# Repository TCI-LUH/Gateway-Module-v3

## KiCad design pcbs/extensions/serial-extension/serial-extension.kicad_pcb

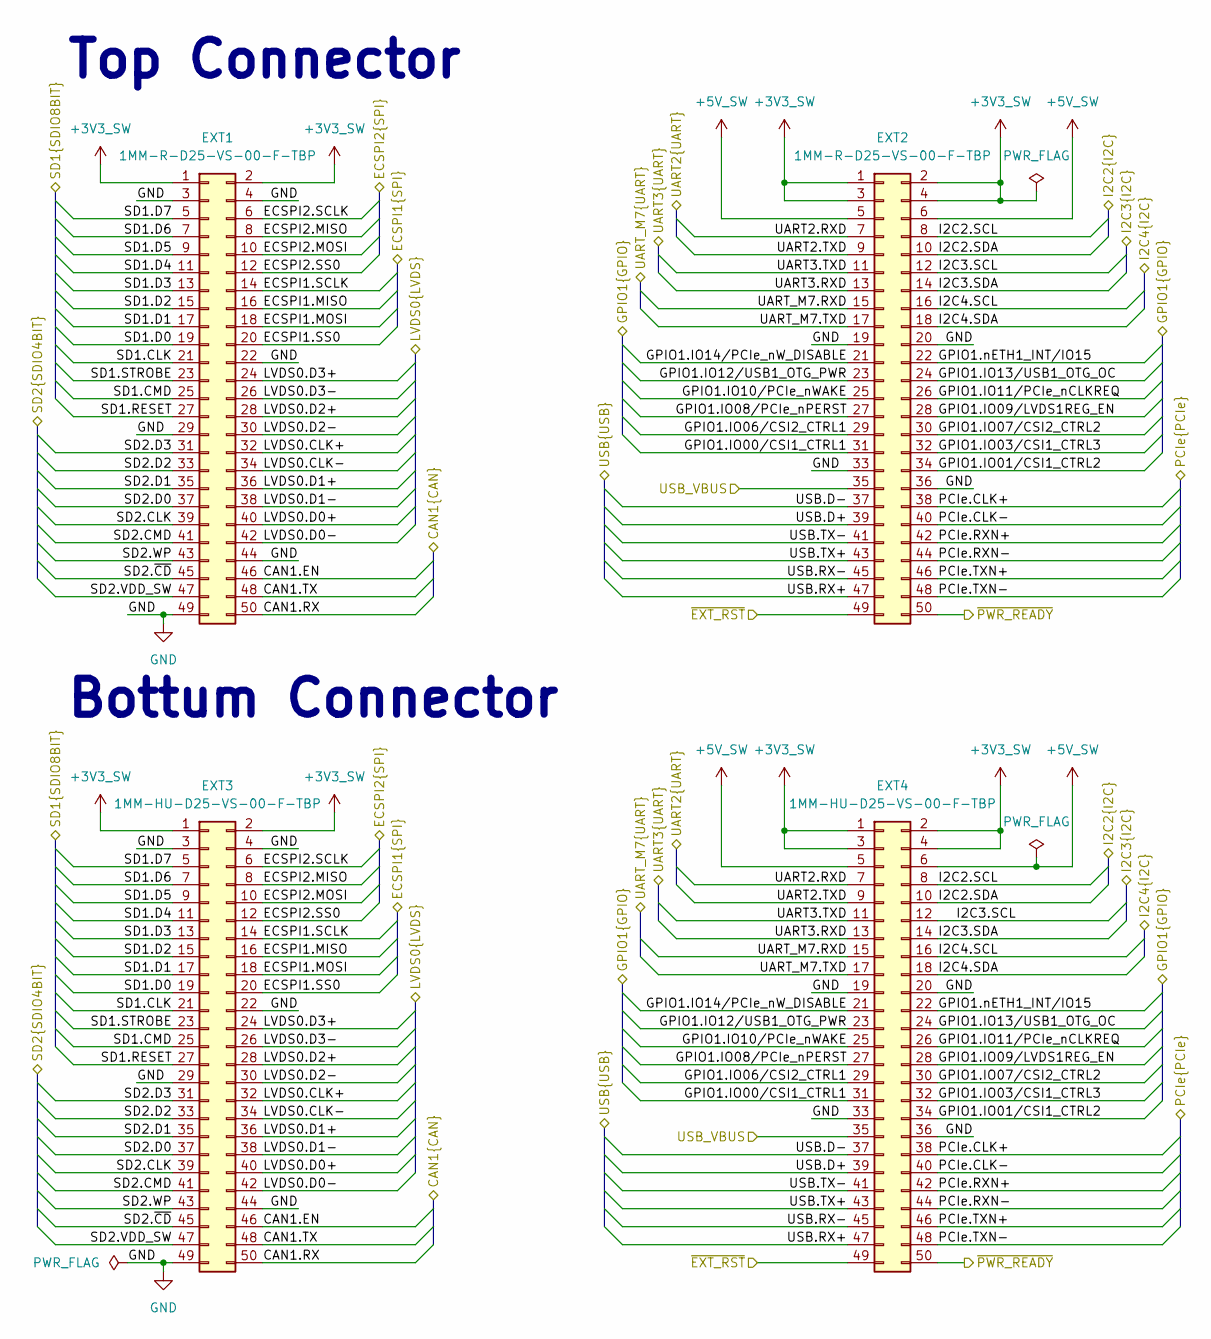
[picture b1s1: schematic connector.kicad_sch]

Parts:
EXT1, EXT2: 1MM-R-D25-VS-00-F-TBP; 1MMRD25VS00FTBP; Mouser Part Number 571-1MMRD25VS00FTBP
EXT3, EXT4: 1MM-HU-D25-VS-00-F-TBP; 1MMHUD25VS00FTBP; Mouser Part Number 571-1MMRD25VS00FTBP

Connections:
+3V3_SW: EXT1.1, EXT1.2, EXT2.1, EXT2.2, EXT2.3, EXT2.4, EXT3.1, EXT3.2, EXT4.1, EXT4.2, EXT4.3, EXT4.4; also elsewhere on the board
+5V_SW: EXT2.5, EXT2.6, EXT4.5, EXT4.6
/connector/CAN1.EN: EXT1.46, EXT3.46
/connector/CAN1.RX: EXT1.50, EXT3.50
/connector/CAN1.TX: EXT1.48, EXT3.48
/connector/ECSPI1.MISO: EXT1.16, EXT3.16
/connector/ECSPI1.MOSI: EXT1.18, EXT3.18
/connector/ECSPI1.SCLK: EXT1.14, EXT3.14
/connector/ECSPI1.SS0: EXT1.20, EXT3.20
/connector/ECSPI2.MISO: EXT1.8, EXT3.8
/connector/ECSPI2.MOSI: EXT1.10, EXT3.10
/connector/ECSPI2.SCLK: EXT1.6, EXT3.6
/connector/ECSPI2.SS0: EXT1.12, EXT3.12
/connector/GPIO1.IO00/CSI1_CTRL1: EXT2.31, EXT4.31
/connector/GPIO1.IO01/CSI1_CTRL2: EXT2.34, EXT4.34
/connector/GPIO1.IO03/CSI1_CTRL3: EXT2.32, EXT4.32
/connector/GPIO1.IO06/CSI2_CTRL1: EXT2.29, EXT4.29
/connector/GPIO1.IO07/CSI2_CTRL2: EXT2.30, EXT4.30
/connector/GPIO1.IO08/PCIe_nPERST: EXT2.27, EXT4.27
/connector/GPIO1.IO09/LVDS1REG_EN: EXT2.28, EXT4.28
/connector/GPIO1.IO10/PCIe_nWAKE: EXT2.25, EXT4.25
/connector/GPIO1.IO11/PCIe_nCLKREQ: EXT2.26, EXT4.26
/connector/GPIO1.IO12/USB1_OTG_PWR: EXT2.23, EXT4.23
/connector/GPIO1.IO13/USB1_OTG_OC: EXT2.24, EXT4.24
/connector/GPIO1.IO14/PCIe_nW_DISABLE: EXT2.21, EXT4.21
/connector/GPIO1.nETH1_INT/IO15: EXT2.22, EXT4.22
/connector/I2C2.SCL: EXT2.8, EXT4.8; also elsewhere on the board
/connector/I2C2.SDA: EXT2.10, EXT4.10; also elsewhere on the board
/connector/I2C3.SCL: EXT2.12, EXT4.12
/connector/I2C3.SDA: EXT2.14, EXT4.14
/connector/I2C4.SCL: EXT2.16, EXT4.16
/connector/I2C4.SDA: EXT2.18, EXT4.18
/connector/LVDS0.CLK+: EXT1.32, EXT3.32
/connector/LVDS0.CLK-: EXT1.34, EXT3.34
/connector/LVDS0.D0+: EXT1.40, EXT3.40
/connector/LVDS0.D0-: EXT1.42, EXT3.42
/connector/LVDS0.D1+: EXT1.36, EXT3.36
/connector/LVDS0.D1-: EXT1.38, EXT3.38
/connector/LVDS0.D2+: EXT1.28, EXT3.28
/connector/LVDS0.D2-: EXT1.30, EXT3.30
/connector/LVDS0.D3+: EXT1.24, EXT3.24
/connector/LVDS0.D3-: EXT1.26, EXT3.26
/connector/PCIe.CLK+: EXT2.38, EXT4.38
/connector/PCIe.CLK-: EXT2.40, EXT4.40
/connector/PCIe.RXN+: EXT2.42, EXT4.42
/connector/PCIe.RXN-: EXT2.44, EXT4.44
/connector/PCIe.TXN+: EXT2.46, EXT4.46
/connector/PCIe.TXN-: EXT2.48, EXT4.48
/connector/SD1.CLK: EXT1.21, EXT3.21
/connector/SD1.CMD: EXT1.25, EXT3.25
/connector/SD1.D0: EXT1.19, EXT3.19
/connector/SD1.D1: EXT1.17, EXT3.17
/connector/SD1.D2: EXT1.15, EXT3.15
/connector/SD1.D3: EXT1.13, EXT3.13
/connector/SD1.D4: EXT1.11, EXT3.11
/connector/SD1.D5: EXT1.9, EXT3.9
/connector/SD1.D6: EXT1.7, EXT3.7
/connector/SD1.D7: EXT1.5, EXT3.5
/connector/SD1.RESET: EXT1.27, EXT3.27
/connector/SD1.STROBE: EXT1.23, EXT3.23
/connector/SD2.CLK: EXT1.39, EXT3.39
/connector/SD2.CMD: EXT1.41, EXT3.41
/connector/SD2.D0: EXT1.37, EXT3.37
/connector/SD2.D1: EXT1.35, EXT3.35
/connector/SD2.D2: EXT1.33, EXT3.33
/connector/SD2.D3: EXT1.31, EXT3.31
/connector/SD2.VDD_SW: EXT1.47, EXT3.47
/connector/SD2.WP: EXT1.43, EXT3.43
/connector/SD2.~CD: EXT1.45, EXT3.45
/connector/UART2.RXD: EXT2.7, EXT4.7; also elsewhere on the board
/connector/UART2.TXD: EXT2.9, EXT4.9; also elsewhere on the board
/connector/UART3.RXD: EXT2.13, EXT4.13; also elsewhere on the board
/connector/UART3.TXD: EXT2.11, EXT4.11; also elsewhere on the board
/connector/UART_M7.RXD: EXT2.15, EXT4.15
/connector/UART_M7.TXD: EXT2.17, EXT4.17
/connector/USB.D+: EXT2.39, EXT4.39
/connector/USB.D-: EXT2.37, EXT4.37
/connector/USB.RX+: EXT2.47, EXT4.47
/connector/USB.RX-: EXT2.45, EXT4.45
/connector/USB.TX+: EXT2.43, EXT4.43
/connector/USB.TX-: EXT2.41, EXT4.41
/connector/USB_VBUS: EXT2.35, EXT4.35
/connector/~EXT_RST: EXT2.49, EXT4.49
/connector/~PWR_READY: EXT2.50, EXT4.50
GND: EXT1.3, EXT1.4, EXT1.22, EXT1.29, EXT1.44, EXT1.49, EXT2.19, EXT2.20, EXT2.33, EXT2.36, EXT3.3, EXT3.4, EXT3.22, EXT3.29, EXT3.44, EXT3.49, EXT4.19, EXT4.20, EXT4.33, EXT4.36; also elsewhere on the board

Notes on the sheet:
Top Connector
Bottum Connector

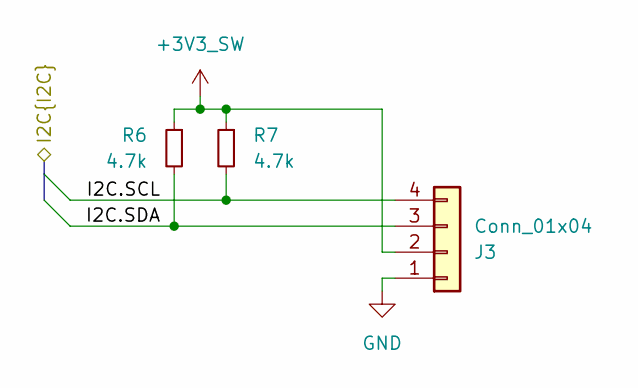
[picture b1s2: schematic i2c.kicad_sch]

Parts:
J3: Conn_01x04; PinHeader_1x04_P1.27mm_Horizontal; Mouser Part Number 437-8501000420001101
R6, R7: 4.7k; R_0402; Mouser Part Number 652-CR0402FX-4701GLF

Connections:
+3V3_SW: J3.2, R6.1, R7.1; also elsewhere on the board
/connector/I2C2.SCL: J3.4, R7.2; also elsewhere on the board
/connector/I2C2.SDA: J3.3, R6.2; also elsewhere on the board
GND: J3.1; also elsewhere on the board

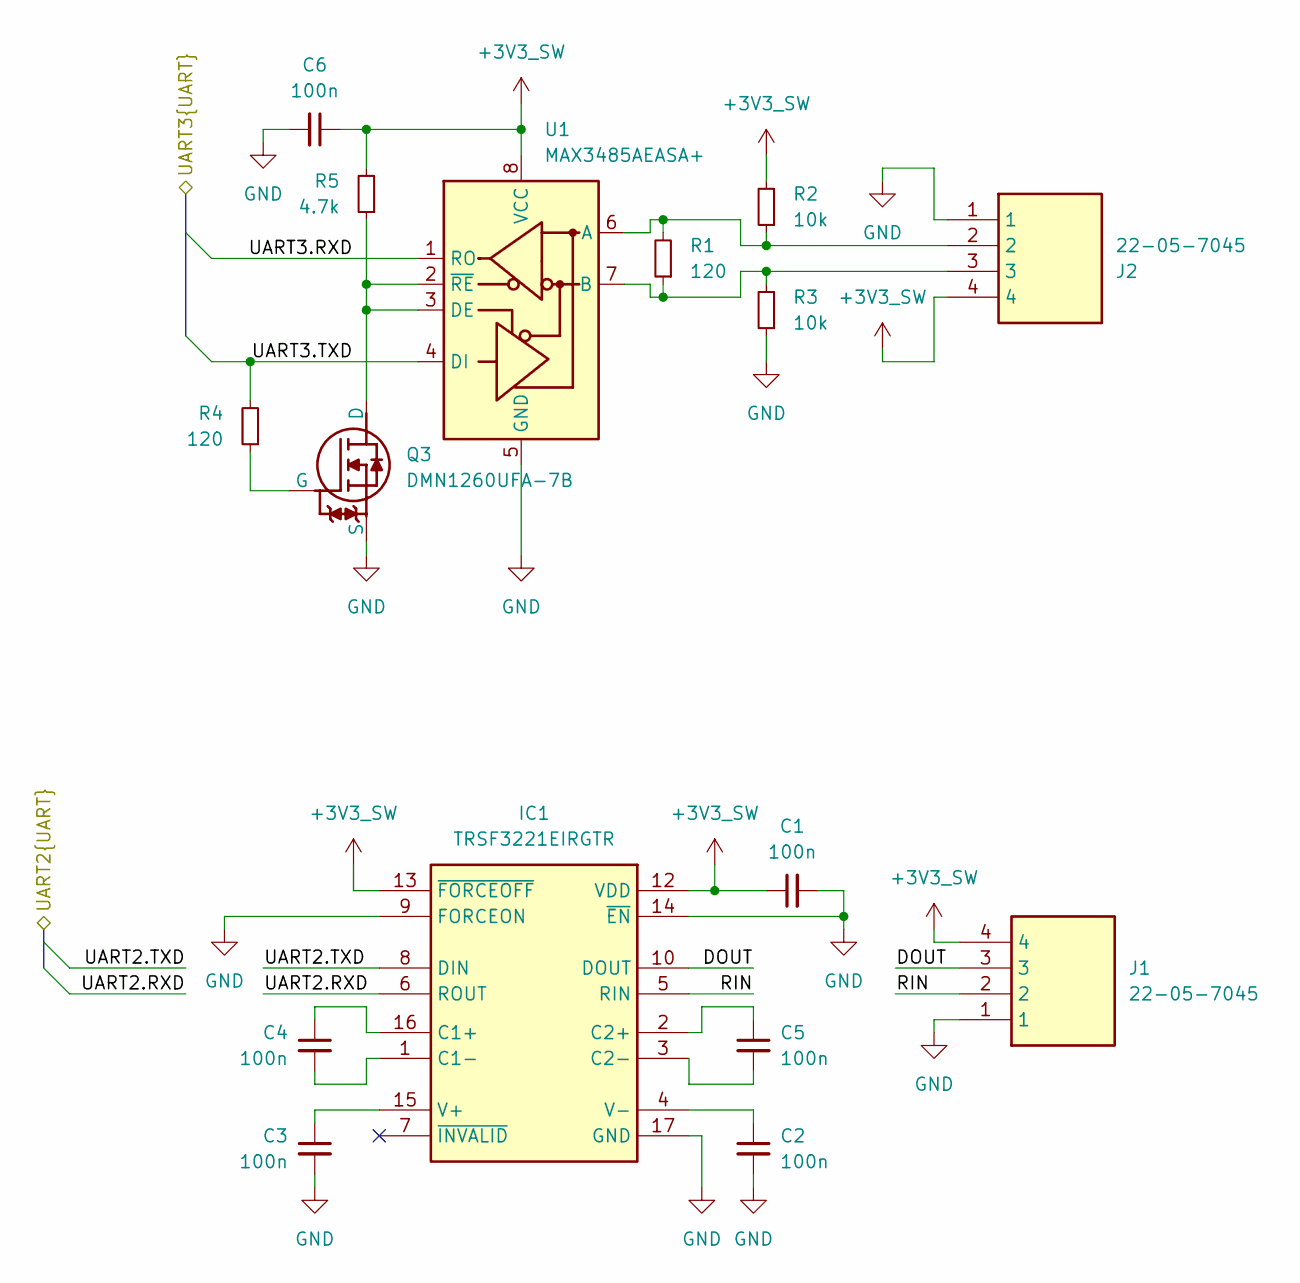
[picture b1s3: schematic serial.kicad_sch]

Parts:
C1, C2, C3, C4, C5, C6: 100n; C_0402; Mouser Part Number 80-C0402C104K4R7867
IC1: TRSF3221EIRGTR; QFN50P300X300X100-17N-D; Mouser Part Number 595-TRSF3221EIRGTR
J1, J2: 22-05-7045; SHDRRA4W45P0X250_1X4_1240X790X510P; Mouser Part Number 538-22-05-7045
Q3: DMN1260UFA-7B; DMN1260UFA7B; Mouser Part Number 621-DMN1260UFA-7B
R1, R4: 120; R_0402; Mouser Part Number 603-AC0402FR-07120RL
R2, R3: 10k; R_0402; Mouser Part Number 652-CR0402AFX1002GAS
R5: 4.7k; R_0402; Mouser Part Number 652-CR0402FX-4701GLF
U1: MAX3485AEASA+; SOIC-8_3.9x4.9mm_P1.27mm; Mouser Part Number 700-MAX3485AEASA+

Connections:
+3V3_SW: C1.1, C6.1, IC1.12 (VDD), IC1.13 (~FORCEOFF), J1.4, J2.4, R2.2, R5.2, U1.8 (VCC); also elsewhere on the board
/connector/UART2.RXD: IC1.6 (ROUT); also elsewhere on the board
/connector/UART2.TXD: IC1.8 (DIN); also elsewhere on the board
/connector/UART3.RXD: U1.1 (RO); also elsewhere on the board
/connector/UART3.TXD: R4.2, U1.4 (DI); also elsewhere on the board
/serial/DOUT: IC1.10 (DOUT), J1.3
/serial/RIN: IC1.5 (RIN), J1.2
GND: C1.2, C2.2, C3.2, C6.2, IC1.9 (FORCEON), IC1.11 (GND), IC1.14 (~EN), IC1.17 (GND), J1.1, J2.1, Q3.2 (S), R3.1, U1.5 (GND); also elsewhere on the board
unnamed: C4.1, IC1.16 (C1+)
unnamed: C4.2, IC1.1 (C1-)
unnamed: C5.1, IC1.2 (C2+)
unnamed: C5.2, IC1.3 (C2-)
unnamed: C3.1, IC1.15 (V+)
unnamed: C2.1, IC1.4 (V-)
unnamed: Q3.3 (D), R5.1, U1.2 (~RE), U1.3 (DE)
unnamed: Q3.1 (G), R4.1
unnamed: J2.2, R1.2, R2.1, U1.6 (A)
unnamed: J2.3, R1.1, R3.2, U1.7 (B)

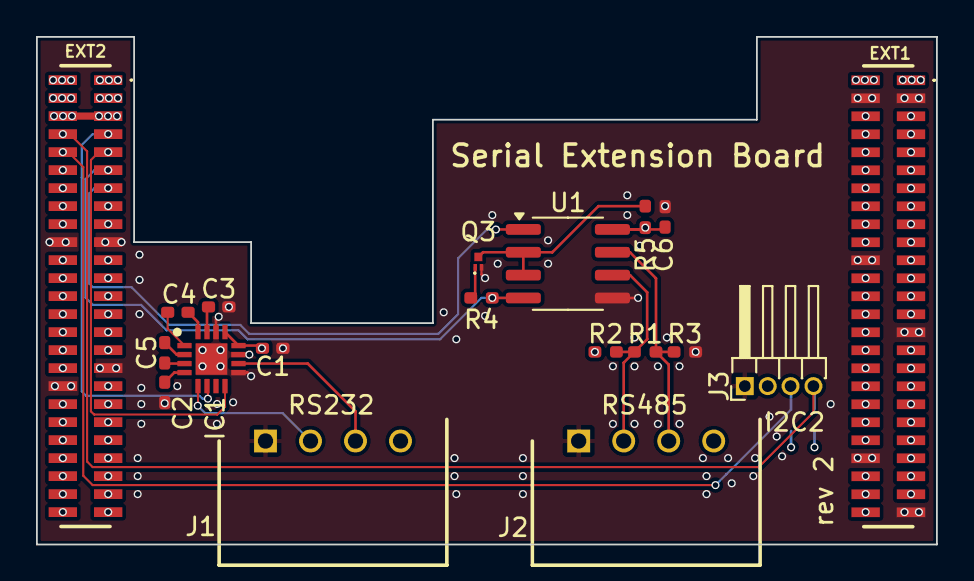
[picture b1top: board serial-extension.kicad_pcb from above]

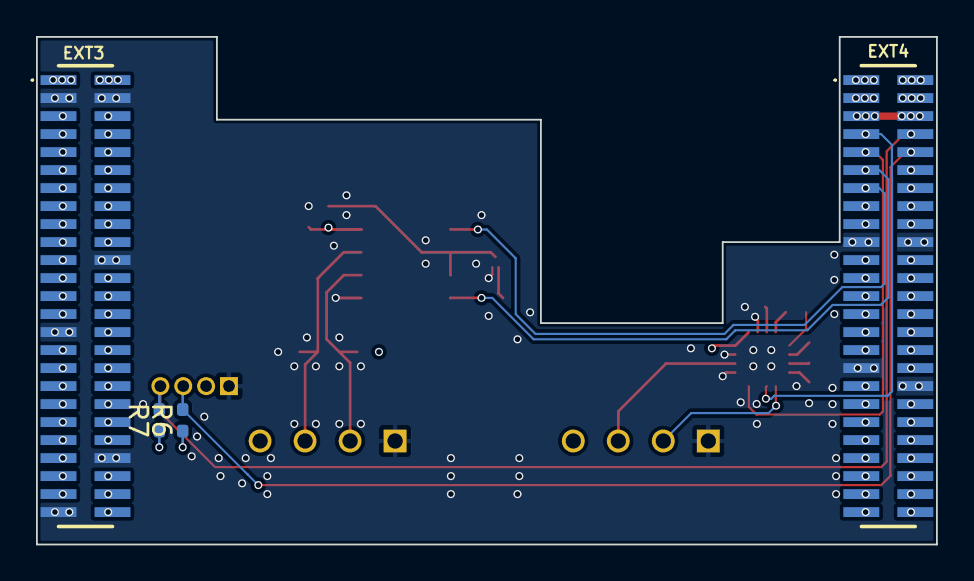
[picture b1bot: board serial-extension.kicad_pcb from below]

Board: 4 copper layers, 50.0 x 28.2 mm, 23 parts (4 on the bottom side), 97 nets.

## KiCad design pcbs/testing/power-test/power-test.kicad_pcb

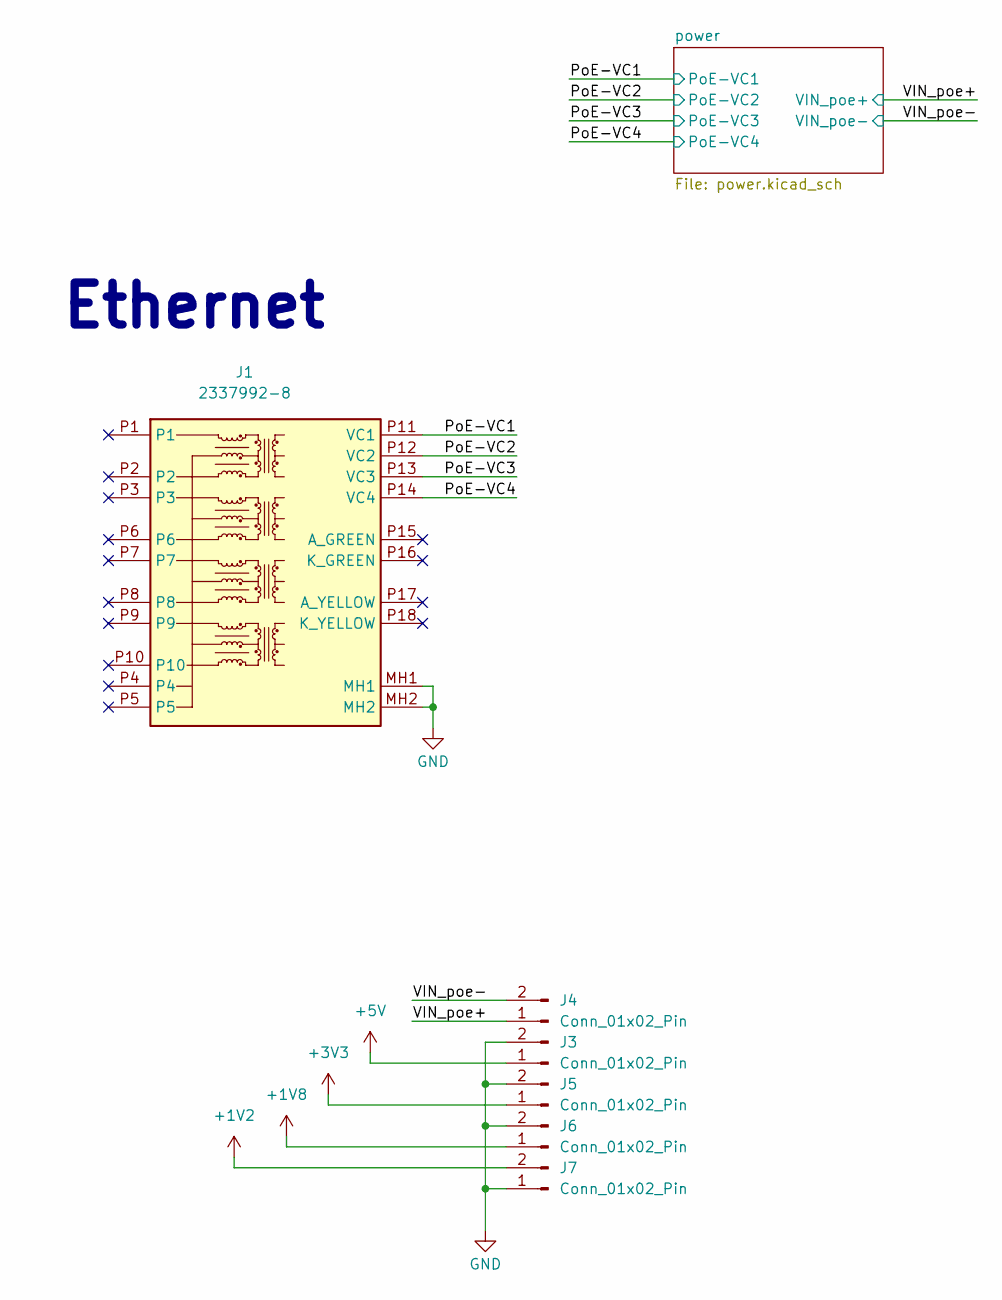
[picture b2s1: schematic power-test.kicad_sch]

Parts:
J1: 2337992-8; 23379928; Mouser Part Number 571-2337992-8
J3, J4, J5, J6, J7: Conn_01x02_Pin; PinHeader_1x02_P2.54mm_Horizontal

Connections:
+1V2: J7.2; also elsewhere on the board
+1V8: J6.1; also elsewhere on the board
+3V3: J5.1; also elsewhere on the board
+5V: J3.1; also elsewhere on the board
/PoE-VC1: J1.P11 (VC1); also elsewhere on the board
/PoE-VC2: J1.P12 (VC2); also elsewhere on the board
/PoE-VC3: J1.P13 (VC3); also elsewhere on the board
/PoE-VC4: J1.P14 (VC4); also elsewhere on the board
/VIN_poe+: J4.1; also elsewhere on the board
/VIN_poe-: J4.2; also elsewhere on the board
GND: J1.MH1, J1.MH2, J3.2, J5.2, J6.2, J7.1; also elsewhere on the board

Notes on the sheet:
Ethernet

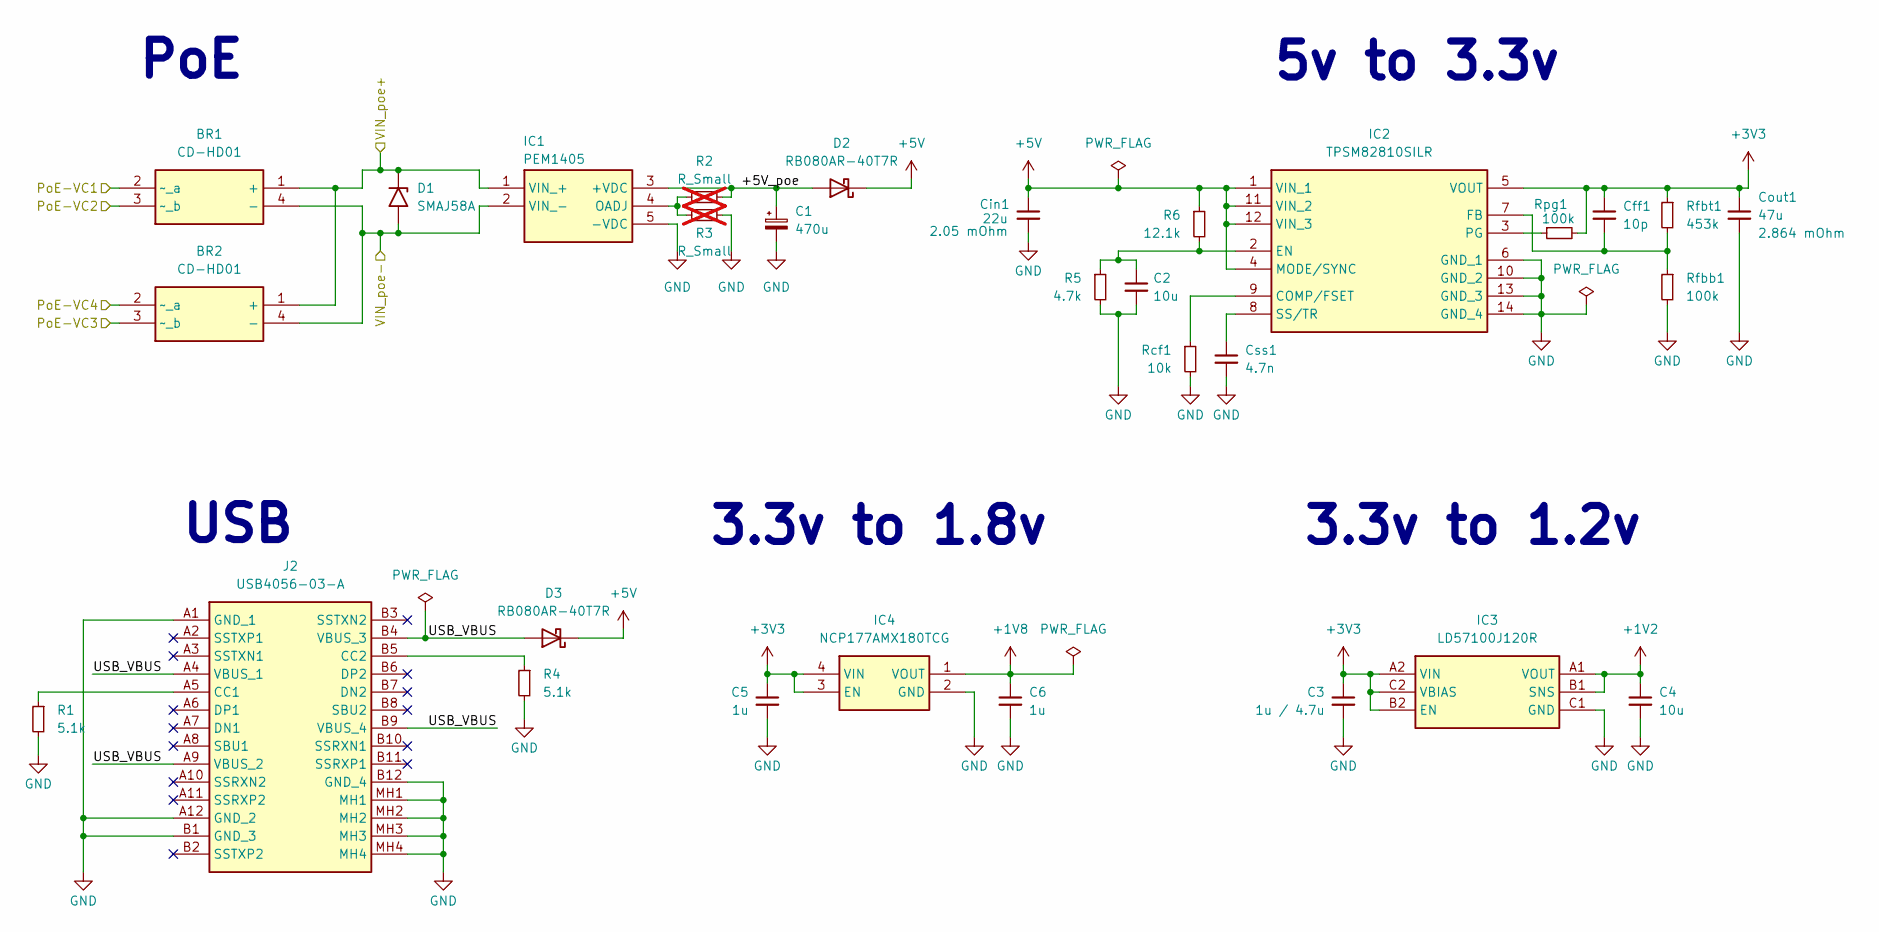
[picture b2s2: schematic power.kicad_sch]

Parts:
BR1, BR2: CD-HD01; CDHD01; Mouser Part Number 652-CD-HD01
C1: 470u; CP_Radial_D6.3mm_P2.50mm; Mouser Part Number 661-APSE6R3L471MF08S
C2: 10u; C_0402_1005Metric_Pad0.74x0.62mm_HandSolder; Mouser Part Number 80-C0603X472J4RECAUT
C3: 1u / 4.7u; C_0402_1005Metric_Pad0.74x0.62mm_HandSolder
C4: 10u; C_0402_1005Metric_Pad0.74x0.62mm_HandSolder
C5, C6: 1u; C_0402_1005Metric_Pad0.74x0.62mm_HandSolder; Mouser Part Number 187-CL05A105KO5NNNC
Cff1: 10p; C_0603_1608Metric_Pad1.08x0.95mm_HandSolder; Mouser Part Number 581-06035A100J
Cin1: 22u; C_0805_2012Metric_Pad1.18x1.45mm_HandSolder; Mouser Part Number 810-C2012X5R1V226MAC
Cout1: 47u; C_1206_3216Metric_Pad1.33x1.80mm_HandSolder; Mouser Part Number 81-GRM32ER71A476KE5L
Css1: 4.7n; C_0603_1608Metric_Pad1.08x0.95mm_HandSolder; Mouser Part Number 80-C0603X472J4RECAUT
D1: SMAJ58A; D_SMA; Mouser Part Number 576-SMAJ58A
D2, D3: RB080AR-40T7R; D_2010_5025Metric_Pad1.52x2.65mm_HandSolder; Mouser Part Number 755-RB080AR-40T7R
IC1: PEM1405; Manufacturer_Part_Number PEM1405
IC2: TPSM82810SILR; Mouser Part Number 595-TPSM82810SILR
IC3: LD57100J120R; BGA6C40P2X3_78X118X36; Mouser Part Number 511-LD57100J120R
IC4: NCP177AMX180TCG; OnSemi_XDFN4-1EP_1.0x1.0mm_EP0.52x0.52mm; Mouser Part Number 863-NCP177AMX180TCG
J2: USB4056-03-A; USB405603A; Mouser Part Number 640-USB4056-03-A
R1, R4: 5.1k; R_0402_1005Metric_Pad0.72x0.64mm_HandSolder
R2, R3: R_Small; R_0402_1005Metric_Pad0.72x0.64mm_HandSolder; not fitted
R5: 4.7k; R_0402_1005Metric_Pad0.72x0.64mm_HandSolder; Mouser Part Number 71-CRCW0402-10K-E3
R6: 12.1k; R_0402_1005Metric_Pad0.72x0.64mm_HandSolder; Mouser Part Number 71-CRCW0402-10K-E3
Rcf1: 10k; R_0402_1005Metric_Pad0.72x0.64mm_HandSolder; Mouser Part Number 71-CRCW0402-10K-E3
Rfbb1: 100k; R_0402_1005Metric_Pad0.72x0.64mm_HandSolder; Mouser Part Number 71-CRCW0402-100K-E3
Rfbt1: 453k; R_0402_1005Metric_Pad0.72x0.64mm_HandSolder; Mouser Part Number 71-CRCW0402-453K-E3
Rpg1: 100k; R_0402_1005Metric_Pad0.72x0.64mm_HandSolder; Mouser Part Number 71-CRCW0402-100K-E3

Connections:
+1V2: C4.1, IC3.A1 (VOUT), IC3.B1 (SNS); also elsewhere on the board
+1V8: C6.1, IC4.1 (VOUT); also elsewhere on the board
+3V3: C3.1, C5.1, Cff1.1, Cout1.1, IC2.5 (VOUT), IC3.A2 (VIN), IC3.B2 (EN), IC3.C2 (VBIAS), IC4.3 (EN), IC4.4 (VIN), Rfbt1.1, Rpg1.2; also elsewhere on the board
+5V: Cin1.1, D2.1 (K), D3.1 (K), IC2.1 (VIN_1), IC2.4 (MODE/SYNC), IC2.11 (VIN_2), IC2.12 (VIN_3), R6.1; also elsewhere on the board
/PoE-VC1: BR1.2 (~_a); also elsewhere on the board
/PoE-VC2: BR1.3 (~_b); also elsewhere on the board
/PoE-VC3: BR2.3 (~_b); also elsewhere on the board
/PoE-VC4: BR2.2 (~_a); also elsewhere on the board
/VIN_poe+: BR1.1 (+), BR2.1 (+), D1.1 (A1), IC1.1 (VIN_+); also elsewhere on the board
/VIN_poe-: BR1.4 (-), BR2.4 (-), D1.2 (A2), IC1.2 (VIN_-); also elsewhere on the board
/power/+5V_poe: C1.1, D2.2 (A), IC1.3 (+VDC), R2.2
/power/USB_VBUS: D3.2 (A), J2.A4 (VBUS_1), J2.A9 (VBUS_2), J2.B4 (VBUS_3), J2.B9 (VBUS_4)
GND: C1.2, C2.2, C3.2, C4.2, C5.2, C6.2, Cin1.2, Cout1.2, Css1.2, IC1.5 (-VDC), IC2.6 (GND_1), IC2.10 (GND_2), IC2.13 (GND_3), IC2.14 (GND_4), IC3.C1 (GND), IC4.2 (GND), IC4.5 (GND), J2.A1 (GND_1), J2.A12 (GND_2), J2.B1 (GND_3), J2.B12 (GND_4), J2.MH1, J2.MH2, J2.MH3, J2.MH4, R1.2, R3.2, R4.2, R5.2, Rcf1.2, Rfbb1.2; also elsewhere on the board
unnamed: IC1.4 (OADJ), R2.1, R3.1
unnamed: IC2.9 (COMP/FSET), Rcf1.1
unnamed: C2.1, IC2.2 (EN), R5.1, R6.2
unnamed: Cff1.2, IC2.7 (FB), Rfbb1.1, Rfbt1.2
unnamed: IC2.3 (PG), Rpg1.1
unnamed: Css1.1, IC2.8 (SS/TR)
unnamed: J2.A5 (CC1), R1.1
unnamed: J2.B5 (CC2), R4.1

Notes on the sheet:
USB
3.3v to 1.8v
3.3v to 1.2v
5v to 3.3v
PoE

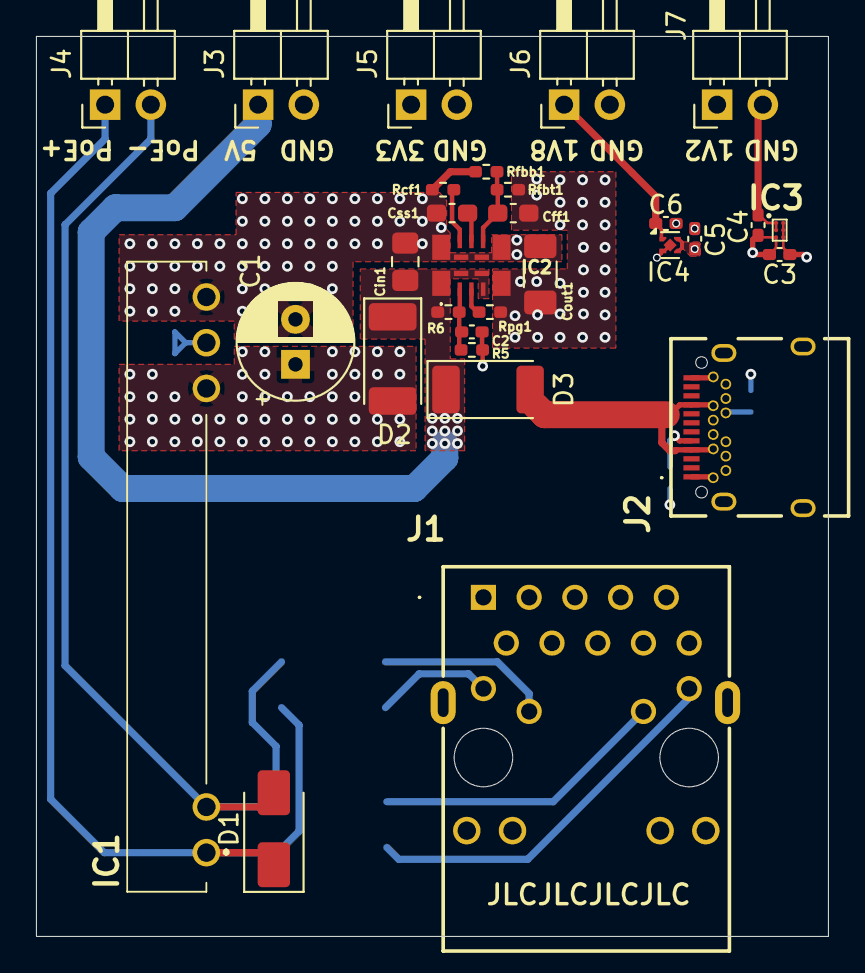
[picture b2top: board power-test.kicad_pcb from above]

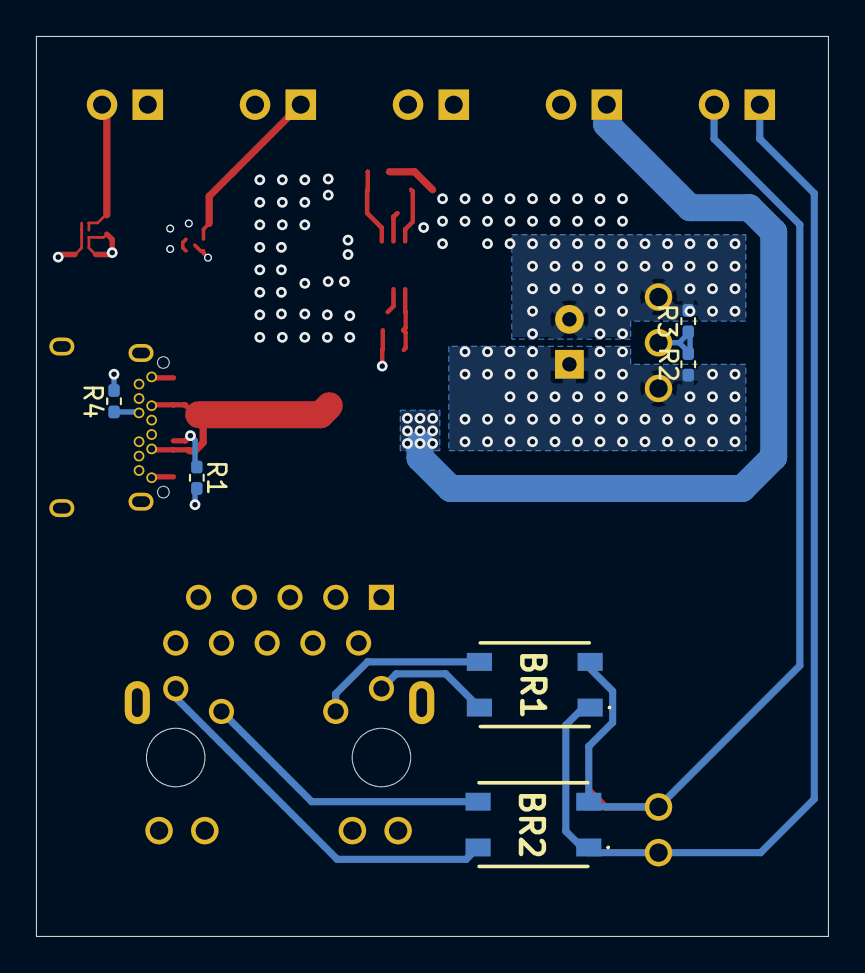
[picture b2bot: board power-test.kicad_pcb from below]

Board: 4 copper layers, 44.0 x 50.0 mm, 36 parts (6 on the bottom side), 21 nets.

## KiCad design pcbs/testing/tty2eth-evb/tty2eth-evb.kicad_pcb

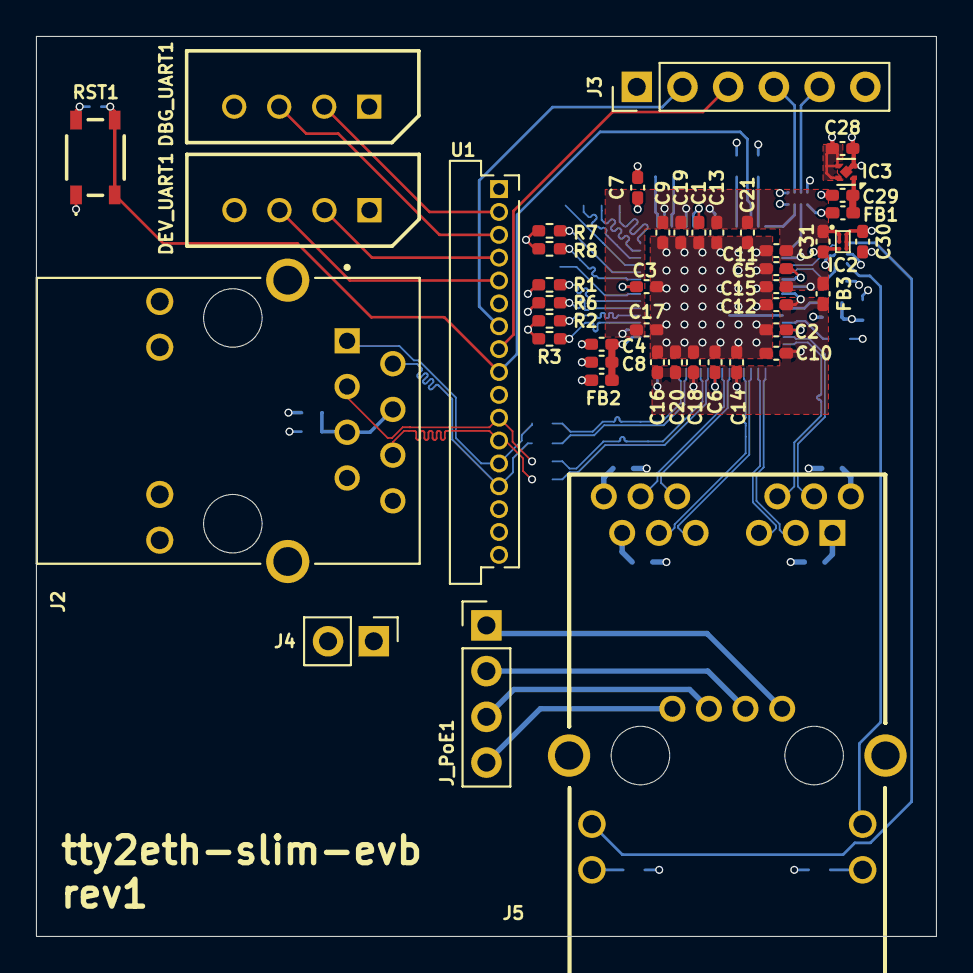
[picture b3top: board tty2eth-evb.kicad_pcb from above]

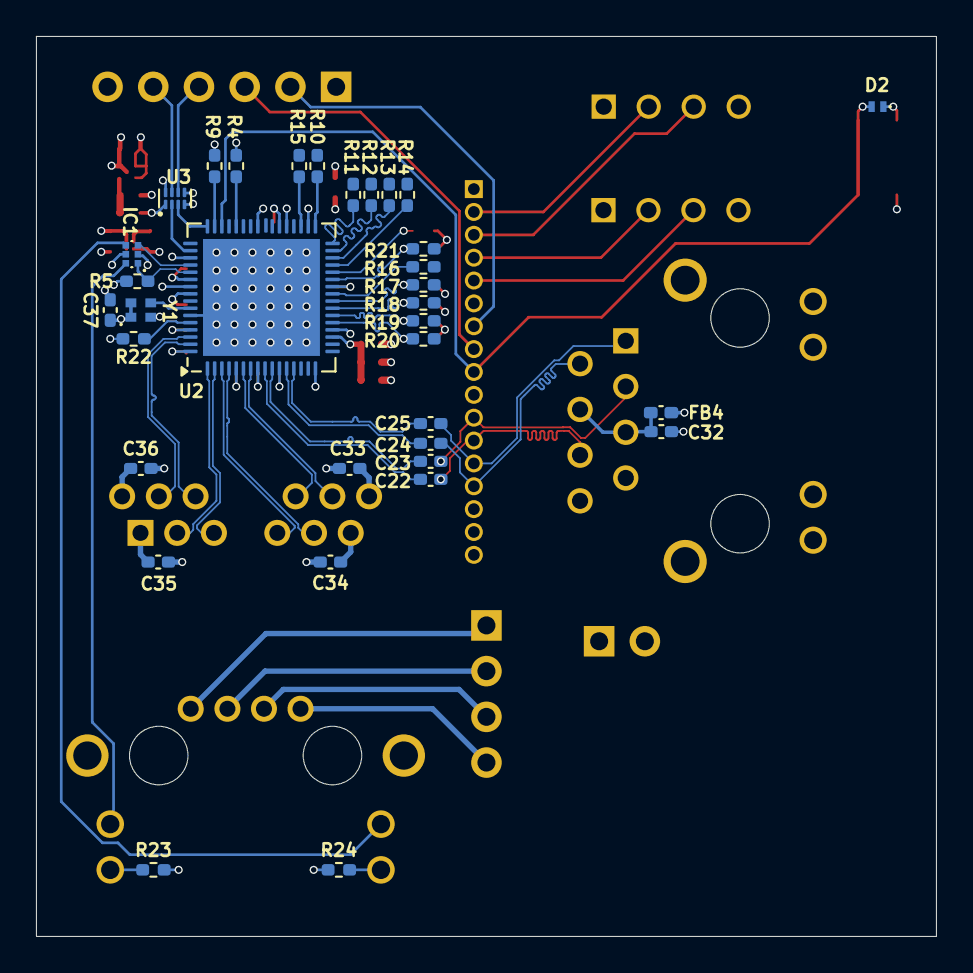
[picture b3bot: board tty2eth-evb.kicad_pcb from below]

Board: 4 copper layers, 50.0 x 50.0 mm, 79 parts (34 on the bottom side), 66 nets.

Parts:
C1, C2, C3, C4, C5, C6, C9, C10, C11, C12, C13, C14, C15, C16, C17, C18, C19, C22, C23, C24, C25, C33, C34, C35, C36, C37: 100n; C_0402_1005Metric_Pad0.74x0.62mm_HandSolder
C7, C8, C20, C21: 22u; C_0402_1005Metric_Pad0.74x0.62mm_HandSolder
C28, C29: 1u; C_0402_1005Metric_Pad0.74x0.62mm_HandSolder
C30: 1u / 4.7u; C_0402_1005Metric_Pad0.74x0.62mm_HandSolder
C31: 10u; C_0402_1005Metric_Pad0.74x0.62mm_HandSolder
C32: 22n; C_0402_1005Metric_Pad0.74x0.62mm_HandSolder
D2: SC1333-01ETG; SC133301ETG
DBG_UART1: 22-03-5045; SHDR4W70P0X250_1X4_1240X490X610P
DEV_UART1: 22-03-5045; SHDR4W70P0X250_1X4_1240X490X610P
FB1, FB2, FB3: BLM15PX121SN1D; L_0402_1005Metric_Pad0.77x0.64mm_HandSolder
FB4: BLM15PE300SH1D; L_0402_1005Metric_Pad0.77x0.64mm_HandSolder
IC1: 74AUP2G07GM; PESD3V3L5UF115
IC2: LD57100J120R; BGA6C40P2X3_78X118X36
IC3: NCP177AMX180TCG; OnSemi_XDFN4-1EP_1.0x1.0mm_EP0.52x0.52mm
J2: CRJ011-ML1-TH; CUI_CRJ011-ML1-TH
J3: Conn_01x06; PinHeader_1x06_P2.54mm_Vertical
J4: Conn_01x02; PinHeader_1x02_P2.54mm_Vertical
J5: JT4-1202HL; JT41202HL
J_PoE1: Conn_01x04; PinHeader_1x04_P2.54mm_Vertical
R1, R2, R3, R4, R5: 4.7k; R_0402_1005Metric_Pad0.72x0.64mm_HandSolder
R6, R7, R8, R9, R23, R24: 1k; R_0402_1005Metric_Pad0.72x0.64mm_HandSolder
R10, R11, R12, R13, R14, R15, R16, R17, R18, R19, R20, R21: 33; R_0402_1005Metric_Pad0.72x0.64mm_HandSolder
R22: 6.04k; R_0402_1005Metric_Pad0.72x0.64mm_HandSolder
RST1: TS20-42-25-WT-160-SMT-TR; TS204225WT160SMTTR
U1: tty2usb-slim; tty2eth-slim
U2: KSZ9563RNX; QFN-64-1EP_8x8mm_P0.4mm_EP6.5x6.5mm
U3: TXS0102DQER; X2SON-8_1.4x1mm_P0.35mm
Y1: ECS-1612MV-250-CN-TR; ECS1612MV250CNTR

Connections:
+1V2: C9.1, C11.1, C13.1, C15.1, C17.1, C19.1, C21.1, C31.1, FB3.1, IC2.A1 (VOUT), IC2.B1 (SNS), U2.20 (DVDDL), U2.34 (DVDDL), U2.37 (DVDDL), U2.41 (DVDDL), U2.51 (DVDDL), U2.55 (DVDDL)
+1V8: C29.1, FB1.1, IC3.1 (VOUT)
+3V3: C28.1, C30.1, DBG_UART1.1, DEV_UART1.1, FB2.1, FB4.2, IC2.A2 (VIN), IC2.B2 (EN), IC2.C2 (VBIAS), IC3.3 (EN), IC3.4 (VIN), J3.1, J4.1, R23.1, R24.1, U1.16 (VDD), U1.17 (VCC), U3.8 (VCCB)
/DBG_UART_RX: DBG_UART1.2, U1.2 (DBG_UART_RX)
/DBG_UART_TX: DBG_UART1.3, U1.3 (DBG_UART_TX)
/DEV_RST: J3.2, U1.7 (DEV_RST)
/DEV_UART_RX: DEV_UART1.3, U1.5 (DEV_UART_RX)
/DEV_UART_TX: DEV_UART1.2, U1.4 (DEV_UART_TX)
/EXT_TMP: J3.3, U1.8 (EXT_TMP)
/PHY_RX+: C23.2, J2.P3 (RXP), U1.11 (PHY_RX+)
/PHY_RX-: C22.2, J2.P6 (RXN), U1.12 (PHY_RX-)
/PHY_TX+: C25.2, J2.P1 (TXP), U1.13 (PHY_TX+)
/PHY_TX-: C24.2, J2.P2 (TXN), U1.14 (PHY_TX-)
/SCL: J3.5, U3.7 (B1)
/SDA: J3.4, U3.6 (B2)
/switch/GRN+: J5.20 (GRN+), R24.2
/switch/GRN-: IC1.4 (2Y), J5.19 (GRN-)
/switch/KDZ_SCL: U2.50 (SCL/MDC), U3.2 (A1)
/switch/KDZ_SDA: U2.48 (SDI/SDA/MDIO), U3.3 (A2)
/switch/KSZ_AVDDH: C2.1, C4.1, C6.1, C8.1, C37.1, FB2.2, U2.8 (AVDDH), U2.19 (AVDDH), U2.61 (AVDDH), Y1.1 (STAND-BY), Y1.4 (VDD)
/switch/KSZ_AVDDL: C10.1, C12.1, C14.1, C16.1, C18.1, C20.1, FB3.2, U2.5 (AVDDL), U2.11 (AVDDL), U2.16 (AVDDL), U2.56 (AVDDL), U2.64 (AVDDL)
/switch/KSZ_LED1_0: IC1.3 (2A), U2.52 (LED1_0)
/switch/KSZ_LED1_1: IC1.1 (1A), R5.2, U2.53 (LED1_1)
/switch/KSZ_RXD0: R1.2, R17.2, U2.24 (RXD0)
/switch/KSZ_RXD1: R6.2, R18.2, U2.23 (RXD1)
/switch/KSZ_RXD2: R2.2, R19.2, U2.22 (RXD2)
/switch/KSZ_RXD3: R3.2, R20.2, U2.21 (RXD3)
/switch/KSZ_RX_CLK: R16.2, U2.25 (RX_CLK/REFCLKO)
/switch/KSZ_RX_CTL: R8.1, R21.2, U2.27 (RX_DV/CRS_DV/RX_CTL)
/switch/KSZ_RX_ER: R7.1, U2.28 (RX_ER)
/switch/KSZ_SDO: R9.1, U2.47 (SDO)
/switch/KSZ_TXD0: R11.2, U2.32 (TXD0)
/switch/KSZ_TXD1: R12.2, U2.31 (TXD1)
/switch/KSZ_TXD2: R13.2, U2.30 (TXD2)
/switch/KSZ_TXD3: R14.2, U2.29 (TXD3)
/switch/KSZ_TX_CLK: R10.2, U2.33 (TX_CLK/REFCLKI)
/switch/KSZ_TX_CTL: R15.2, U2.35 (TX_EN/TX_CTL)
/switch/KSZ_VDDIO: C1.1, C3.1, C5.1, C7.1, FB1.2, IC1.5 (VCC), R1.1, R2.1, R3.1, R4.1, R5.1, U2.26 (VDDIO), U2.38 (VDDIO), U2.54 (VDDIO), U3.1 (VCCA), U3.5 (OE)
/switch/KSZ_~PME: R4.2, U2.44 (~PME)
/switch/TRP1: J5.13 (TRP1), J_PoE1.1
/switch/TRP2: J5.14 (TRP2), J_PoE1.2
/switch/TRP3: J5.15 (TRP3), J_PoE1.3
/switch/TRP4: J5.16 (TRP4), J_PoE1.4
/switch/TXRX1A+: J5.8 (TRD1+), U2.62 (TXRX1P_A)
/switch/TXRX1A-: J5.9 (TRD1-), U2.63 (TXRX1M_A)
/switch/TXRX1B+: J5.2 (TRD2+), U2.1 (TXRX1P_B)
/switch/TXRX1B-: J5.3 (TRD2-), U2.2 (TXRX1M_B)
/switch/TXRX1C+: J5.4 (TRD3+), U2.3 (TXRX1P_C)
/switch/TXRX1C-: J5.5 (TRD3-), U2.4 (TXRX1M_C)
/switch/TXRX1D+: J5.10 (TRD4+), U2.6 (TXRX1P_D)
/switch/TXRX1D-: J5.11 (TRD4-), U2.7 (TXRX1M_D)
/switch/TXRX2A+: C22.1, U2.9 (TXRX2P_A)
/switch/TXRX2A-: C23.1, U2.10 (TXRX2M_A)
/switch/TXRX2B+: C24.1, U2.12 (TXRX2P_B)
/switch/TXRX2B-: C25.1, U2.13 (TXRX2M_B)
/switch/YEL+: J5.18 (YEL+), R23.2
/switch/YEL-: IC1.6 (1Y), J5.17 (YEL-)
/~RST: D2.2, RST1.3 (COM_1), RST1.4 (COM_2), U1.9 (~RST), U2.46 (~RESET)
GND: C1.2, C2.2, C3.2, C4.2, C5.2, C6.2, C7.2, C8.2, C9.2, C10.2, C11.2, C12.2, C13.2, C14.2, C15.2, C16.2, C17.2, C18.2, C19.2, C20.2, C21.2, C28.2, C29.2, C30.2, C31.2, C32.2, C33.2, C34.2, C35.2, C36.2, C37.2, D2.1, DBG_UART1.4, DEV_UART1.4, IC1.2 (GND), IC2.C1 (GND), IC3.2 (GND), IC3.5 (GND), J2.P8 (GND), J2.S1 (SHIELD), J2.S2 (SHIELD__1), J3.6, J4.2, J5.SH, R6.1, R7.2, R8.2, R9.2, R22.2, RST1.1 (NO_1), RST1.2 (NO_2), U1.1 (GND), U1.6 (GND), U1.10 (GND), U1.15 (GND), U2.59 (GND), U2.65 (GND), U3.4 (GND), Y1.2 (GND)
unnamed: C32.1, FB4.1, J2.P4 (TXCT), J2.P5 (RXCT)
unnamed: C36.1, J5.7 (TRCT1)
unnamed: C35.1, J5.1 (TRCT2)
unnamed: C34.1, J5.6 (TRCT3)
unnamed: C33.1, J5.12 (TRCT4)
unnamed: R22.1, U2.60 (ISET)
unnamed: U2.58 (XI), Y1.3 (OUT)

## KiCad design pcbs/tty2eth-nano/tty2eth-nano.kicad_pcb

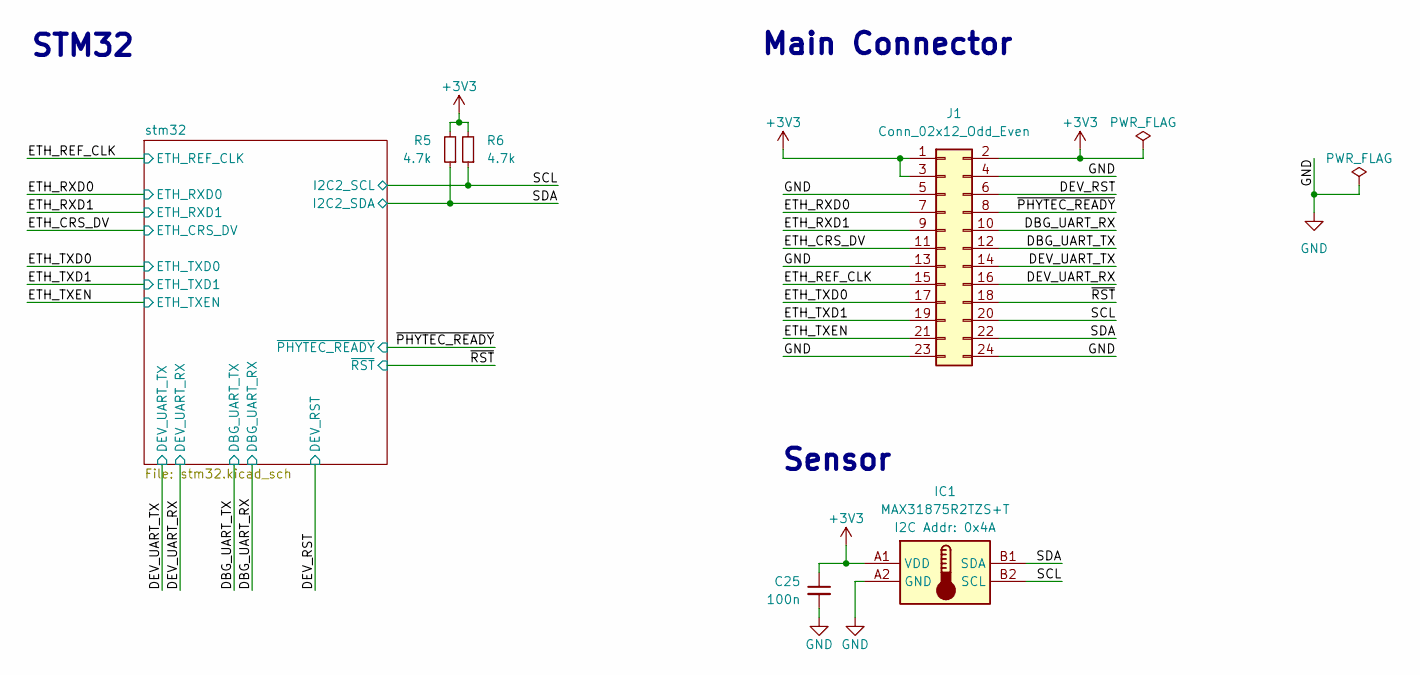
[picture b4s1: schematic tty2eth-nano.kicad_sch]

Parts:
C25: 100n; C_0402; Mouser Part Number 80-C0402C104K4R7867
IC1: MAX31875R2TZS+T; BGA4C40P2X2_84X84X37; Manufacturer_Part_Number MAX31875R2TZS+T; Mouser Part Number 700-MAX31875R2TZS+T
J1: Conn_02x12_Odd_Even; PinHeader_2x12_P1.27mm_Horizontal; Mouser Part Number 200-FTSH11204FDRA
R5, R6: 4.7k; R_0402; Mouser Part Number 652-CR0402FX-47R0GLF

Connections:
+3V3: C25.1, IC1.A1 (VDD), J1.1, J1.2, J1.3, R5.2, R6.2; also elsewhere on the board
/DBG_UART_RX: J1.10; also elsewhere on the board
/DBG_UART_TX: J1.12; also elsewhere on the board
/DEV_RST: J1.6; also elsewhere on the board
/DEV_UART_RX: J1.16; also elsewhere on the board
/DEV_UART_TX: J1.14; also elsewhere on the board
/ETH_CRS_DV: J1.11; also elsewhere on the board
/ETH_REF_CLK: J1.15; also elsewhere on the board
/ETH_RXD0: J1.7; also elsewhere on the board
/ETH_RXD1: J1.9; also elsewhere on the board
/ETH_TXD0: J1.17; also elsewhere on the board
/ETH_TXD1: J1.19; also elsewhere on the board
/ETH_TXEN: J1.21; also elsewhere on the board
/SCL: IC1.B2 (SCL), J1.20, R6.1; also elsewhere on the board
/SDA: IC1.B1 (SDA), J1.22, R5.1; also elsewhere on the board
/~PHYTEC_READY: J1.8; also elsewhere on the board
/~RST: J1.18; also elsewhere on the board
GND: C25.2, IC1.A2 (GND), J1.4, J1.5, J1.13, J1.23, J1.24; also elsewhere on the board

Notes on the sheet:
STM32
Sensor
Main Connector
